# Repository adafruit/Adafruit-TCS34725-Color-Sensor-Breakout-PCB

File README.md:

## Adafruit TCS34725 Color Sensor Breakout PCBs
&nbsp; <br />
Click to purchase from the Adafruit Shop:
- [RGB Color Sensor](https://www.adafruit.com/product/1334)
- [Flora Color Sensor](https://www.adafruit.com/product/1356)

We found the best color sensor on the market, the TCS34725, which has RGB and Clear light sensing elements. An IR blocking filter, integrated on-chip and localized to the color sensing photodiodes, minimizes the IR spectral component of the incoming light and allows color measurements to be made accurately. The filter means you'll get much truer color than most sensors, since humans don't see IR. The sensor also has an incredible 3,800,000:1 dynamic range with adjustable integration time and gain so it is suited for use behind darkened glass.

PCB files for the Adafruit TCS34725 Color Sensor Breakouts - 
Format is EagleCAD schematic and board layout

### License

Adafruit invests time and resources providing this open source design, please support Adafruit and open-source hardware by purchasing products from [Adafruit](https://www.adafruit.com)!

All text above must be included in any redistribution

Designed by Limor Fried/Ladyada for Adafruit Industries.
Creative Commons Attribution/Share-Alike, all text above must be included in any redistribution. 
See license.txt for additional information.

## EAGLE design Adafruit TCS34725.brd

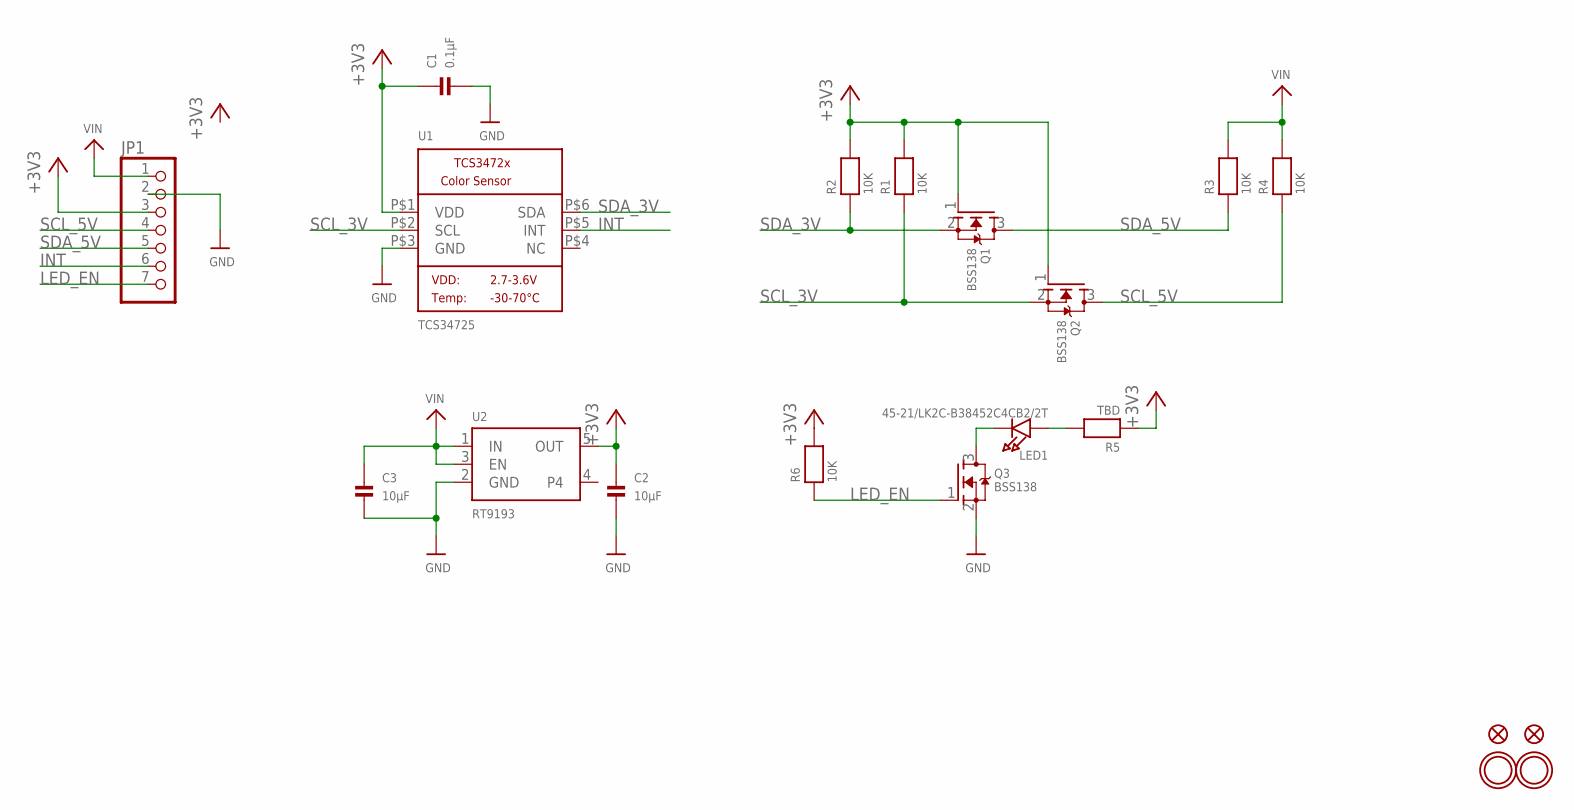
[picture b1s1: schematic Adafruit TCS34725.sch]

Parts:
C1: 0.1µF; _0805
C2, C3: 10µF; _0805
FID1, FID2: FIDUCIAL""; FIDUCIAL_1MM
JP1: HEADER-1X770MIL; 1X07_ROUND_70
LED1: 45-21/LK2C-B38452C4CB2/2T; EVERLIGHT_45-21
Q1, Q2, Q3: BSS138; SOT23-WIDE
R1, R2, R3, R4, R6: 10K; _0805
R5: TBD; _0805
U1: TCS34725; TCS3472_FN6
U2: RT9193; SOT23-5
U$8, U$14: MOUNTINGHOLE2.5; MOUNTINGHOLE_2.5_PLATED

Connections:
+3V3: C1.1, C2.1, JP1.3, Q1.1 (G), Q2.1 (G), R1.2, R2.2, R5.1, R6.2, U1.P$1 (VDD), U2.5 (OUT)
GND: C1.2, C2.2, C3.2, JP1.2, Q3.2 (S), U1.P$3 (GND), U2.2 (GND)
INT: JP1.6, U1.P$5 (INT)
LED_EN: JP1.7, Q3.1 (G), R6.1
unnamed: LED1.K (C), Q3.3 (D)
unnamed: LED1.A, R5.2
SCL_3V: Q2.2 (S), R1.1, U1.P$2 (SCL)
SCL_5V: JP1.4, Q2.3 (D), R4.1
SDA_3V: Q1.2 (S), R2.1, U1.P$6 (SDA)
SDA_5V: JP1.5, Q1.3 (D), R3.1
VIN: C3.1, JP1.1, R3.2, R4.2, U2.1 (IN), U2.3 (EN)

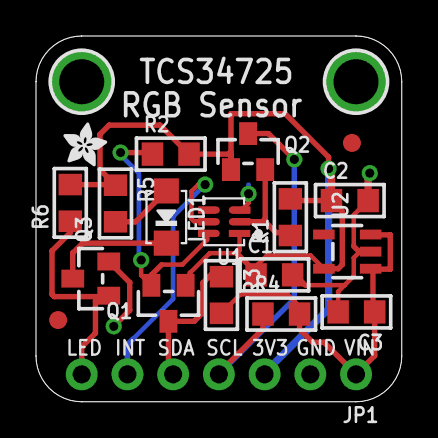
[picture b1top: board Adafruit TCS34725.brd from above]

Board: 2 copper layers, 20.3 x 20.3 mm, 22 parts (1 on the bottom side), 11 nets.

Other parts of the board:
U$2: ADAFRUIT_2.5MM
U$18: ADAFRUIT_5MM

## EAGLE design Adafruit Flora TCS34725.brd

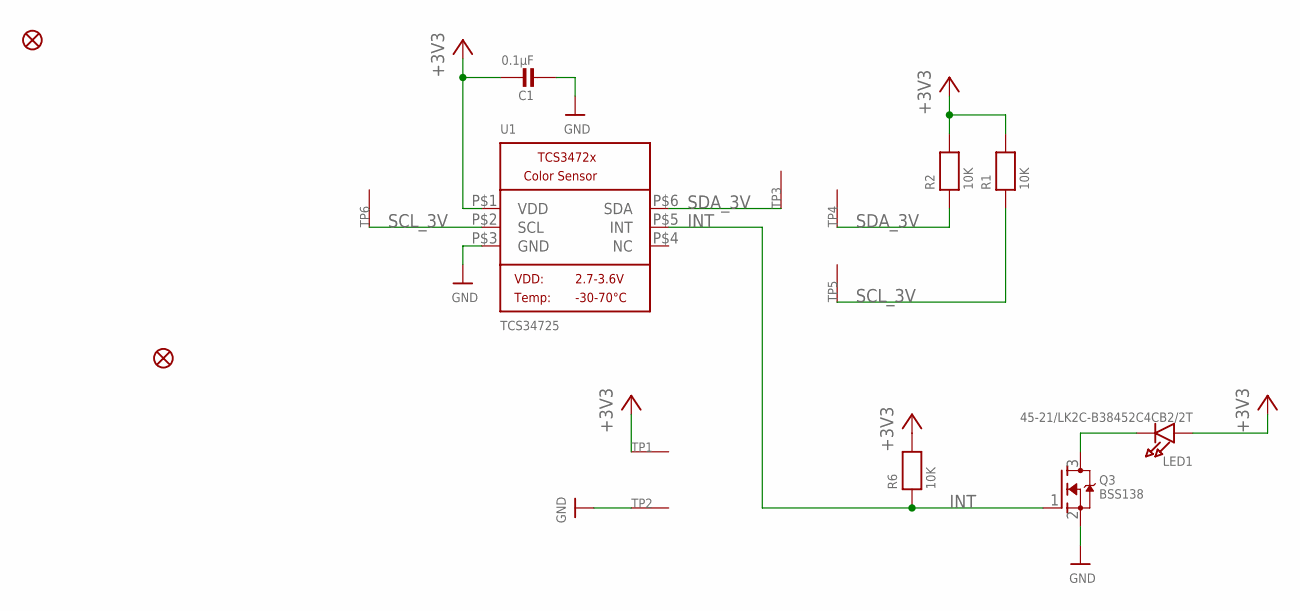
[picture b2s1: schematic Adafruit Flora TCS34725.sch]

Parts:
C1: 0.1µF; _0805
FID1, FID2: FIDUCIAL""; FIDUCIAL_1MM
LED1: 45-21/LK2C-B38452C4CB2/2T; EVERLIGHT_45-21
Q3: BSS138; SOT23-WIDE
R1, R2, R6: 10K; _0805
TP1, TP2, TP3, TP4, TP5, TP6: SEWTAP0.5IN; SEWINGTAP_0.5
U1: TCS34725; TCS3472_FN6

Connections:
+3V3: C1.1, LED1.A, R1.2, R2.2, R6.2, TP1.TAP, U1.P$1 (VDD)
GND: C1.2, Q3.2 (S), TP2.TAP, U1.P$3 (GND)
INT: Q3.1 (G), R6.1, U1.P$5 (INT)
unnamed: LED1.K (C), Q3.3 (D)
SCL_3V: R1.1, TP5.TAP, TP6.TAP, U1.P$2 (SCL)
SDA_3V: R2.1, TP3.TAP, TP4.TAP, U1.P$6 (SDA)

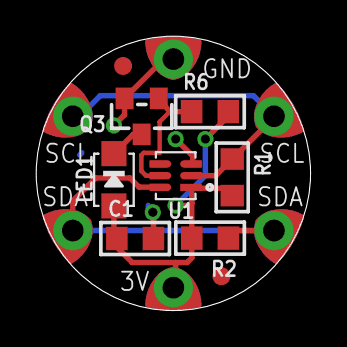
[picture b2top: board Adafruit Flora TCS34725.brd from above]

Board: 2 copper layers, 15.2 x 15.2 mm, 16 parts (1 on the bottom side), 6 nets.

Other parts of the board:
U$8: ADAFRUIT_3.5MM

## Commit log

2014-12-20 pcb files!
2014-12-20 add urls

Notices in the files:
parts and their libraries:
microbuilder: This work is placed in the public domain, and may be freely used for commercial and non-commercial work with the following conditions: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
